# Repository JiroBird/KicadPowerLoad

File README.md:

The rights to the circuit design belong to: 
https://www.youtube.com/c/akakasyan

The project presents a vision of PCB implementation by JiroBird.

!!! NOTICE !!!!
The project uses a super diode 80EBU02, the cathode of which is directly connected to the drain of the super transistor IRGPS40B120U through cooling plates

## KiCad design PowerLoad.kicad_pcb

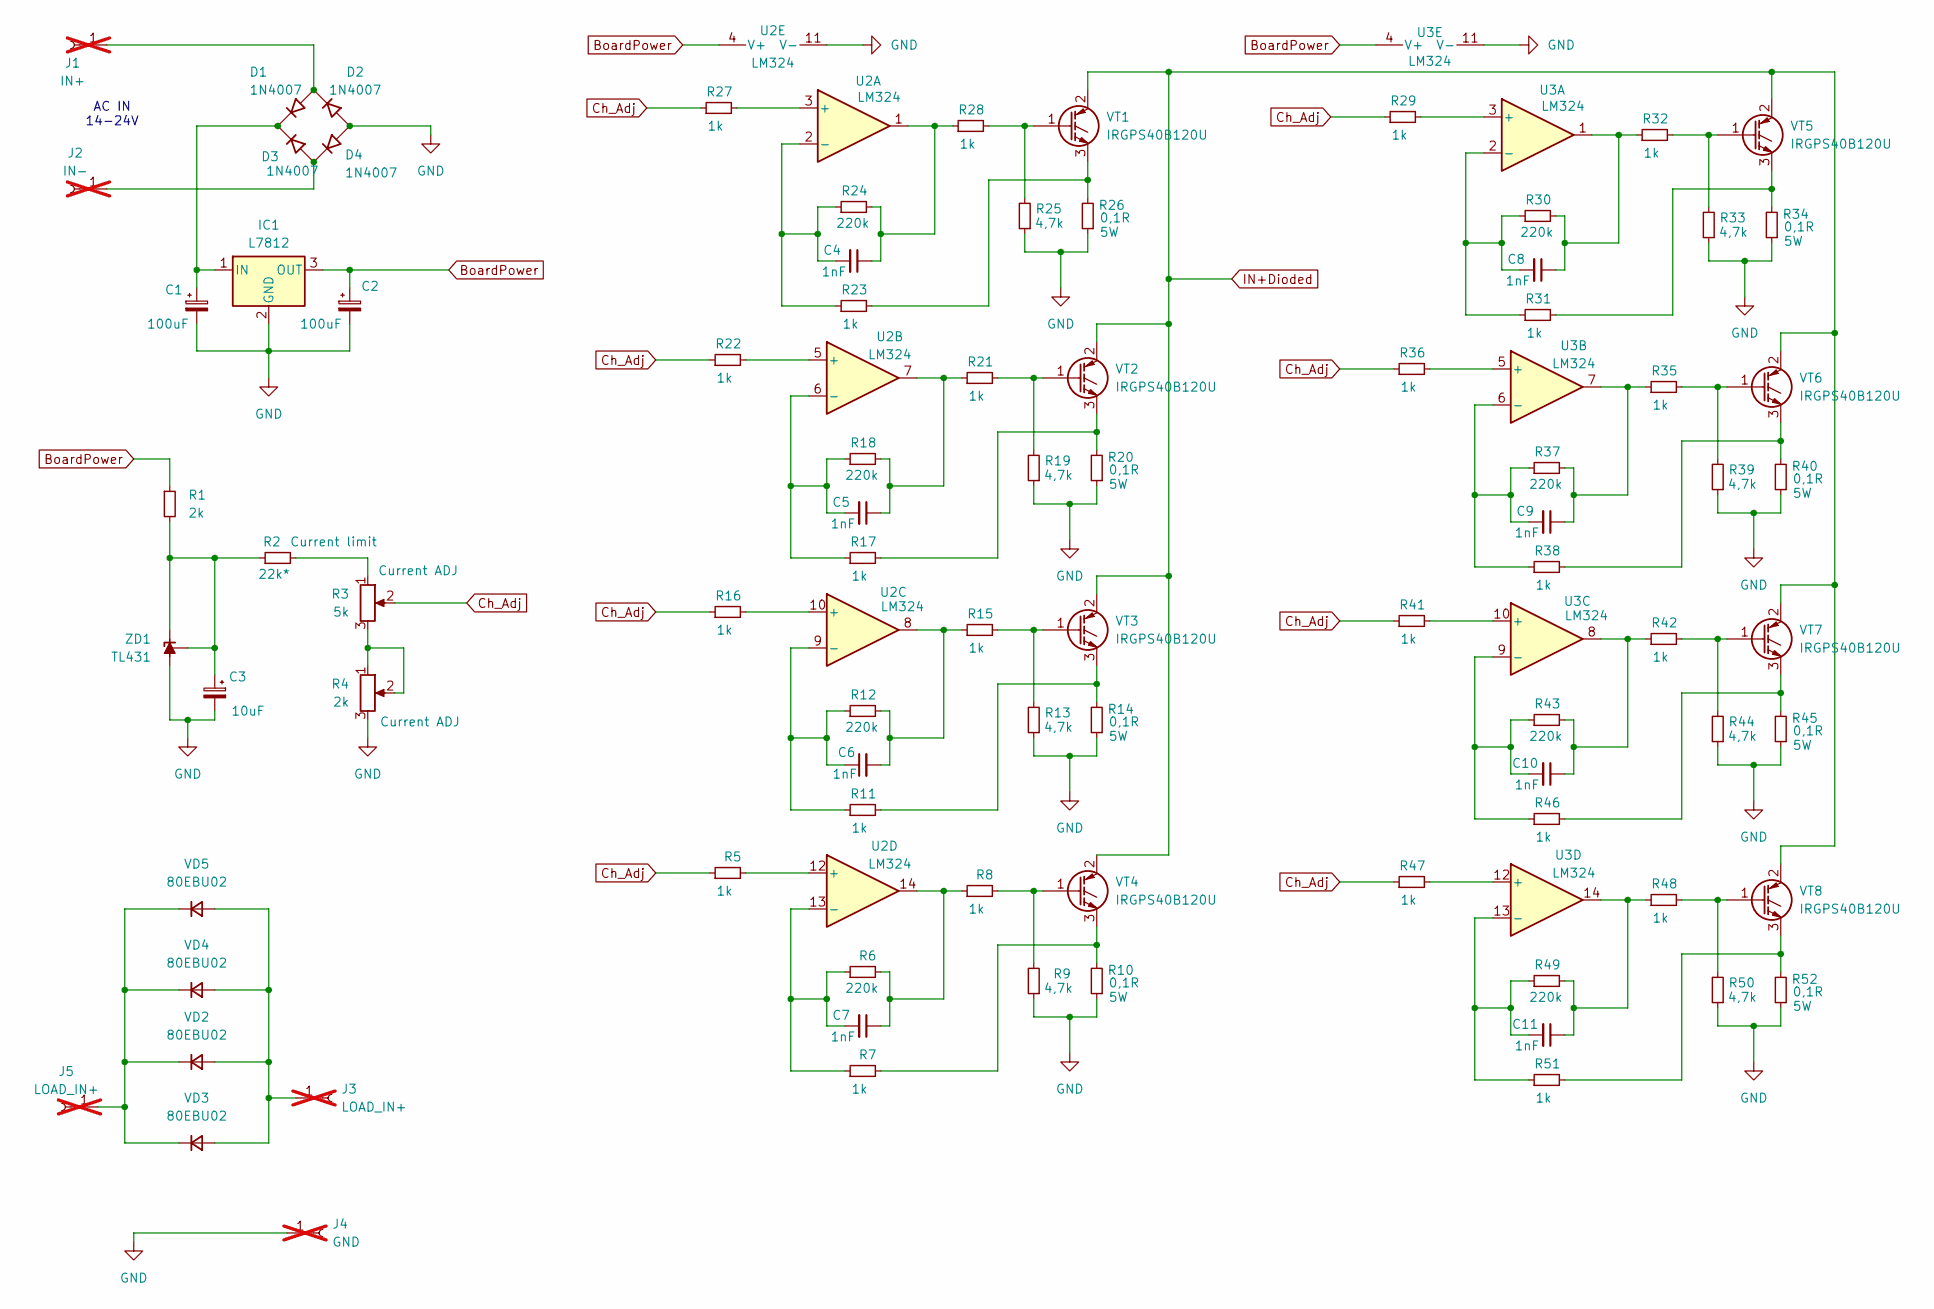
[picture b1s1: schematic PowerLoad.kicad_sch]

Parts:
C1, C2: 100uF; CP_Radial_D8.0mm_P3.80mm
C3: 10uF; CP_Radial_D5.0mm_P2.50mm
C4, C5, C6, C7, C8, C9, C10, C11: 1nF; C_Axial_L3.8mm_D2.6mm_P7.50mm_Horizontal
D1, D2, D3, D4: 1N4007; D_DO-41_SOD81_P10.16mm_Horizontal
IC1: L7812; TO-220-3_Vertical
J1: IN+; SolderWire-2.5sqmm_1x01_D2.4mm_OD4.4mm; not fitted
J2: IN-; SolderWire-2.5sqmm_1x01_D2.4mm_OD4.4mm; not fitted
J3, J5: LOAD_IN+; SolderWire-16sqmm_1x01_D8.5mm_OD12mm; not fitted
J4: GND; SolderWire-16sqmm_1x01_D8.5mm_OD12mm; not fitted
R1: 2k; R_Axial_DIN0204_L3.6mm_D1.6mm_P7.62mm_Horizontal
R2: 22k*; R_Axial_DIN0204_L3.6mm_D1.6mm_P7.62mm_Horizontal
R3: 5k; Potentiometer_Bourns_3386F_Vertical
R4: 2k; Potentiometer_Bourns_3386F_Vertical
R5, R7, R8, R11, R15, R16, R17, R21, R22, R23, R27, R28, R29, R31, R32, R35, R36, R38, R41, R42, R46, R47, R48, R51: 1k; R_Axial_DIN0204_L3.6mm_D1.6mm_P7.62mm_Horizontal
R6, R12, R18, R24, R30, R37, R43, R49: 220k; R_Axial_DIN0204_L3.6mm_D1.6mm_P7.62mm_Horizontal
R9, R13, R19, R25, R33, R39, R44, R50: 4,7k; R_Axial_DIN0204_L3.6mm_D1.6mm_P7.62mm_Horizontal
R10, R14, R20, R26, R34, R40, R45, R52: 0,1R; R_Axial_DIN0309_L9.0mm_D3.2mm_P25.40mm_Horizontal
U2, U3: LM324; DIP-14_W7.62mm_LongPads
VD2, VD3, VD4, VD5: 80EBU02; TO-247-3(powirtab)
VT1, VT2, VT3, VT4, VT5, VT6, VT7, VT8: IRGPS40B120U; TO-247-3_Vertical
ZD1: TL431; TO-92_Inline

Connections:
BoardPower: C2.1, IC1.3 (OUT), R1.1, U2.4 (V+), U3.4 (V+)
Ch_Adj: R3.2, R5.1, R16.1, R22.1, R27.1, R29.1, R36.1, R41.1, R47.1
GND: C1.2, C2.2, C3.2, D2.2 (A), D4.2 (A), IC1.2 (GND), J4.1, R4.3, R9.1, R10.1, R13.1, R14.1, R19.1, R20.1, R25.1, R26.1, R33.1, R34.1, R39.1, R40.1, R44.1, R45.1, R50.1, R52.1, U2.11 (V-), U3.11 (V-), ZD1.2 (A)
IN+Dioded: VT1.2 (C), VT2.2 (C), VT3.2 (C), VT4.2 (C), VT5.2 (C), VT6.2 (C), VT7.2 (C), VT8.2 (C)
unnamed: C4.1, R24.2, R28.1, U2.1
unnamed: C5.1, R18.2, R21.1, U2.7
unnamed: C6.2, R12.2, R15.1, U2.8
unnamed: C7.1, R6.2, R8.1, U2.14
unnamed: C8.1, R30.2, R32.1, U3.1
unnamed: C9.1, R35.1, R37.2, U3.7
unnamed: C10.1, R42.1, R43.2, U3.8
unnamed: C11.1, R48.1, R49.2, U3.14
unnamed: D1.2 (A), D2.1 (K), J1.1
unnamed: C1.1, D1.1 (K), D3.1 (K), IC1.1 (IN)
unnamed: D3.2 (A), D4.1 (K), J2.1
unnamed: J3.1, VD2.2 (A), VD3.2 (A), VD4.2 (A), VD5.2 (A)
unnamed: J5.1, VD2.1 (K), VD3.1 (K), VD4.1 (K), VD5.1 (K)
unnamed: R2.2, R3.1
unnamed: R3.3, R4.1, R4.2
unnamed: R27.2, U2.3 (+)
unnamed: C4.2, R23.1, R24.1, U2.2 (-)
unnamed: R22.2, U2.5 (+)
unnamed: C5.2, R17.1, R18.1, U2.6 (-)
unnamed: R16.2, U2.10 (+)
unnamed: C6.1, R11.1, R12.1, U2.9 (-)
unnamed: R5.2, U2.12 (+)
unnamed: C7.2, R6.1, R7.1, U2.13 (-)
unnamed: R29.2, U3.3 (+)
unnamed: C8.2, R30.1, R31.1, U3.2 (-)
unnamed: R36.2, U3.5 (+)
unnamed: C9.2, R37.1, R38.1, U3.6 (-)
unnamed: R41.2, U3.10 (+)
unnamed: C10.2, R43.1, R46.1, U3.9 (-)
unnamed: R47.2, U3.12 (+)
unnamed: C11.2, R49.1, R51.1, U3.13 (-)
unnamed: R23.2, R26.2, VT1.3 (E)
unnamed: R25.2, R28.2, VT1.1 (G)
unnamed: R17.2, R20.2, VT2.3 (E)
unnamed: R19.2, R21.2, VT2.1 (G)
unnamed: R11.2, R14.2, VT3.3 (E)
unnamed: R13.2, R15.2, VT3.1 (G)
unnamed: R7.2, R10.2, VT4.3 (E)
unnamed: R8.2, R9.2, VT4.1 (G)
unnamed: R31.2, R34.2, VT5.3 (E)
unnamed: R32.2, R33.2, VT5.1 (G)
unnamed: R38.2, R40.2, VT6.3 (E)
unnamed: R35.2, R39.2, VT6.1 (G)
unnamed: R45.2, R46.2, VT7.3 (E)
unnamed: R42.2, R44.2, VT7.1 (G)
unnamed: R51.2, R52.2, VT8.3 (E)
unnamed: R48.2, R50.2, VT8.1 (G)
unnamed: C3.1, R1.2, R2.1, ZD1.1 (REF), ZD1.3 (K)

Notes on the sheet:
AC IN 14-24V

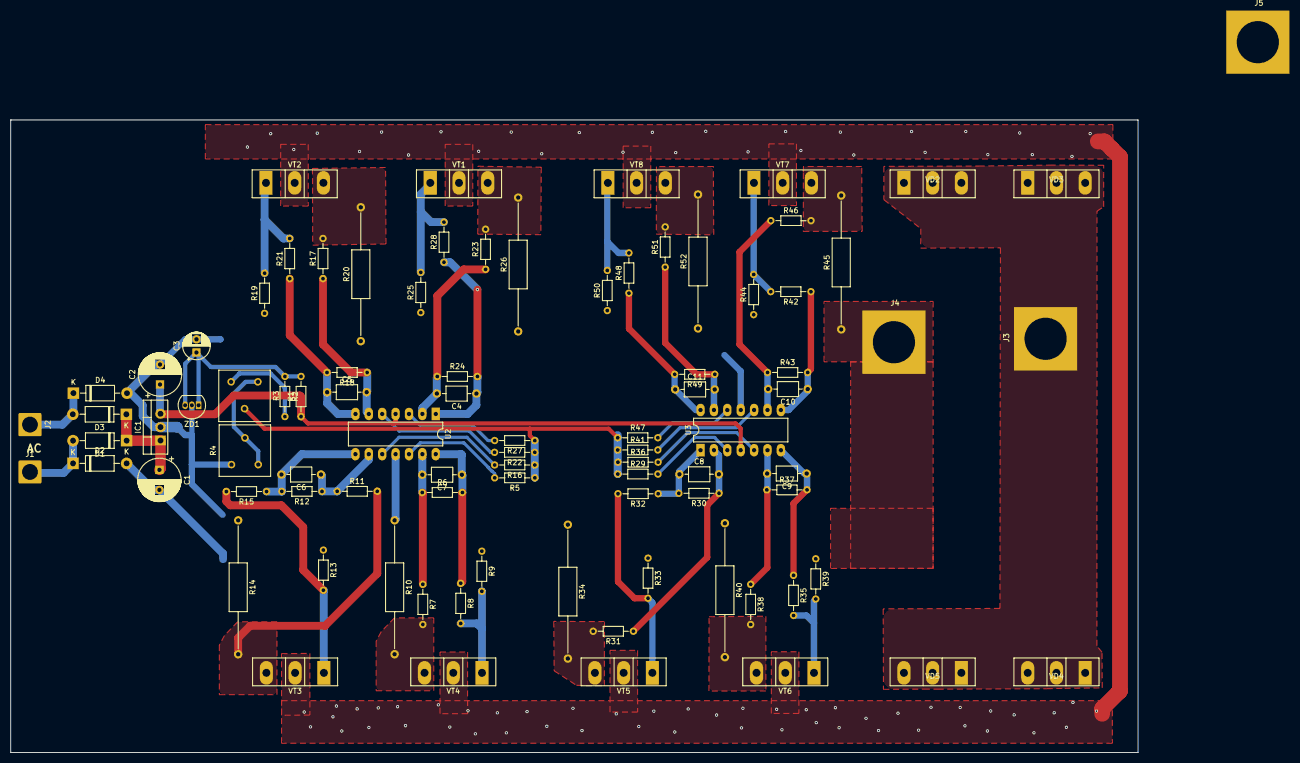
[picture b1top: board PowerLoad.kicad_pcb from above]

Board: 2 copper layers, 213.9 x 120.0 mm, 88 parts (0 on the bottom side), 51 nets.

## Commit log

2025-07-03 v_0.0.1
2025-07-03 README.md added
2025-07-03 added NOTICE
2025-07-03 fixed super TO247-3
